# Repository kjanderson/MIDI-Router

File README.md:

# MIDI-Router
PIC24/FPGA code to route MIDI data on prototype hardware.

The objective of this project is to build a prototype that is able to route MIDI
signals from source to destination automatically.

The hardware provides 4 MIDI inputs, 4 MIDI thru's, and 4 MIDI outputs.
This software project implements the routing of the inputs to the outputs.

Notes
 - USB is copied from the MLA USB Framework
 - USB-app is copied from the application example in the MLA
 - USB-bsp is copied from the application example in the MLA

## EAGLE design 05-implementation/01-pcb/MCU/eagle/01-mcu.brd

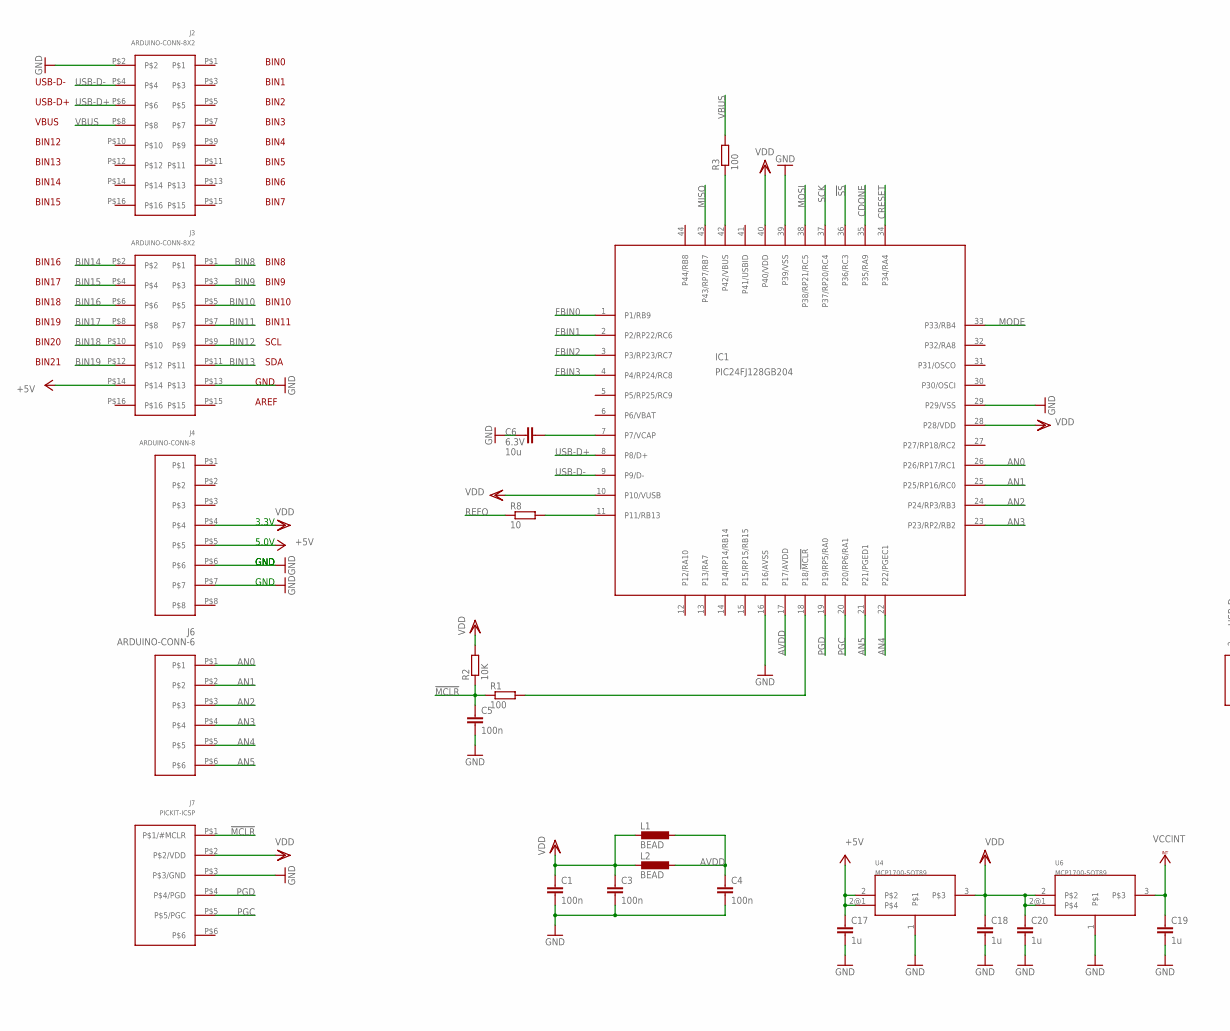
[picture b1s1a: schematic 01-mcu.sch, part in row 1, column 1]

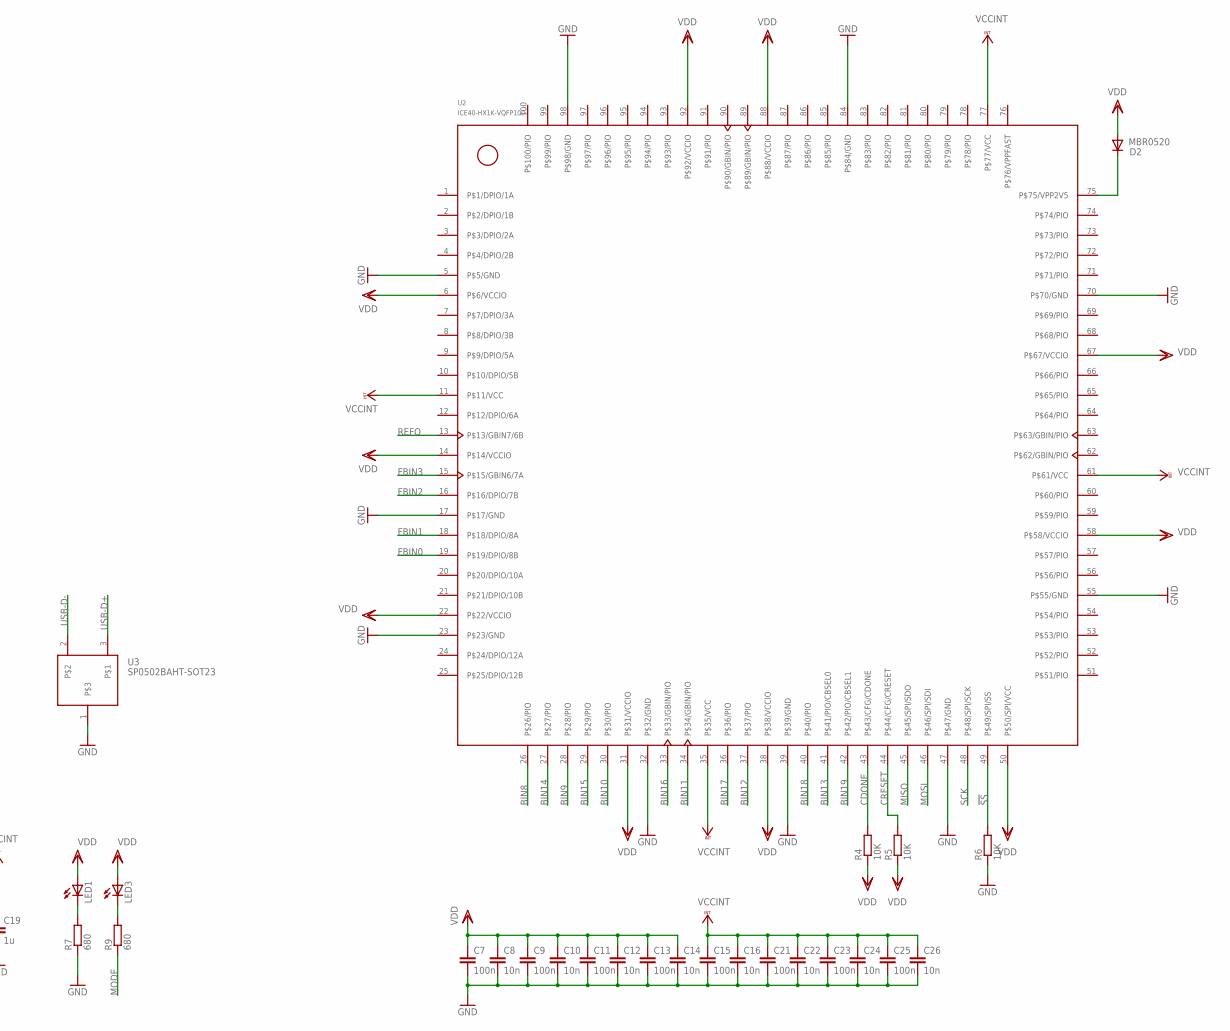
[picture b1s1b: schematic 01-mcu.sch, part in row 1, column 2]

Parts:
C1, C3, C4, C5, C7, C9, C11, C13, C15, C21, C23, C25: 100n; C0805
C6: 10u; C0805; RATING 6.3V
C8, C10, C12, C14, C16, C22, C24, C26: 10n; C0805
C17, C18, C19, C20: 1u; C0805
D2: MBR0520; MBR0520-SOD-123_MINI-SMA
IC1: PIC24FJ128GB204; TQFP44
J2, J3: ARDUINO-CONN-8X2
J4: ARDUINO-CONN-8
J6: ARDUINO-CONN-6
J7: PICKIT-ICSP
L1, L2: BEAD; L0805
LED1, LED3: LEDCHIP-LED0805; CHIP-LED0805
R1, R3: 100; R0805
R2, R4, R5, R6: 10K; R0805
R7, R9: 680; R0805
R8: 10; R0805
U2: ICE40-HX1K-VQFP100; TQFP100-14X14
U3: SP0502BAHT-SOT23; SOT23
U4, U6: MCP1700-SOT89

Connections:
!MCLR: C5.1, J7.P$1 (P$1/#MCLR), R1.1, R2.1
!SS: IC1.36 (P36/RC3), R6.2, U2.49 (P$49/SPI/SS)
+5V: C17.1, J3.P$14, J4.P$5, U4.2, U4.2@1
AN0: IC1.26 (P26/RP17/RC1), J6.P$1
AN1: IC1.25 (P25/RP16/RC0), J6.P$2
AN2: IC1.24 (P24/RP3/RB3), J6.P$3
AN3: IC1.23 (P23/RP2/RB2), J6.P$4
AN4: IC1.22 (P22/PGEC1), J6.P$5
AN5: IC1.21 (P21/PGED1), J6.P$6
AVDD: C4.1, IC1.17 (P17/AVDD), L1.2, L2.2
BIN8: J3.P$1, U2.26 (P$26/PIO)
BIN9: J3.P$3, U2.28 (P$28/PIO)
BIN10: J3.P$5, U2.30 (P$30/PIO)
BIN11: J3.P$7, U2.34 (P$34/GBIN/PIO)
BIN12: J3.P$9, U2.37 (P$37/PIO)
BIN13: J3.P$11, U2.41 (P$41/PIO/CBSEL0)
BIN14: J3.P$2, U2.27 (P$27/PIO)
BIN15: J3.P$4, U2.29 (P$29/PIO)
BIN16: J3.P$6, U2.33 (P$33/GBIN/PIO)
BIN17: J3.P$8, U2.36 (P$36/PIO)
BIN18: J3.P$10, U2.40 (P$40/PIO)
BIN19: J3.P$12, U2.42 (P$42/PIO/CBSEL1)
CDONE: IC1.35 (P35/RA9), R4.2, U2.43 (P$43/CFG/CDONE)
CRESET: IC1.34 (P34/RA4), R5.2, U2.44 (P$44/CFG/CRESET)
FBIN0: IC1.1 (P1/RB9), U2.19 (P$19/DPIO/8B)
FBIN1: IC1.2 (P2/RP22/RC6), U2.18 (P$18/DPIO/8A)
FBIN2: IC1.3 (P3/RP23/RC7), U2.16 (P$16/DPIO/7B)
FBIN3: IC1.4 (P4/RP24/RC8), U2.15 (P$15/GBIN6/7A)
GND: C1.2, C3.2, C4.2, C5.2, C6.1, C7.2, C8.2, C9.2, C10.2, C11.2, C12.2, C13.2, C14.2, C15.2, C16.2, C17.2, C18.2, C19.2, C20.2, C21.2, C22.2, C23.2, C24.2, C25.2, C26.2, IC1.16 (P16/AVSS), IC1.29 (P29/VSS), IC1.39 (P39/VSS), J2.P$2, J3.P$13, J4.P$6, J4.P$7, J7.P$3 (P$3/GND), R6.1, R7.1, U2.5 (P$5/GND), U2.17 (P$17/GND), U2.23 (P$23/GND), U2.32 (P$32/GND), U2.39 (P$39/GND), U2.47 (P$47/GND), U2.55 (P$55/GND), U2.70 (P$70/GND), U2.84 (P$84/GND), U2.98 (P$98/GND), U3.1, U4.1, U6.1
MISO: IC1.43 (P43/RP7/RB7), U2.45 (P$45/SPI/SDO)
MODE: IC1.33 (P33/RB4), R9.1
MOSI: IC1.38 (P38/RP21/RC5), U2.46 (P$46/SPI/SDI)
unnamed: IC1.42 (P42/VBUS), R3.1
unnamed: D2.C, U2.75 (P$75/VPP2V5)
unnamed: IC1.18 (P18/!MCLR), R1.2
unnamed: IC1.11 (P11/RB13), R8.2
unnamed: C6.2, IC1.7 (P7/VCAP)
unnamed: LED1.C, R7.2
unnamed: LED3.C, R9.2
PGC: IC1.20 (P20/RP6/RA1), J7.P$5 (P$5/PGC)
PGD: IC1.19 (P19/RP5/RA0), J7.P$4 (P$4/PGD)
REFO: R8.1, U2.13 (P$13/GBIN7/6B)
SCK: IC1.37 (P37/RP20/RC4), U2.48 (P$48/SPI/SCK)
USB-D+: IC1.8 (P8/D+), J2.P$6, U3.3
USB-D-: IC1.9 (P9/D-), J2.P$4, U3.2
VBUS: J2.P$8, R3.2
VCCINT: C15.1, C16.1, C19.1, C21.1, C22.1, C23.1, C24.1, C25.1, C26.1, U2.11 (P$11/VCC), U2.35 (P$35/VCC), U2.61 (P$61/VCC), U2.77 (P$77/VCC), U6.3
VDD: C1.1, C3.1, C7.1, C8.1, C9.1, C10.1, C11.1, C12.1, C13.1, C14.1, C18.1, C20.1, D2.A, IC1.10 (P10/VUSB), IC1.28 (P28/VDD), IC1.40 (P40/VDD), J4.P$4, J7.P$2 (P$2/VDD), L1.1, L2.1, LED1.A, LED3.A, R2.2, R4.1, R5.1, U2.6 (P$6/VCCIO), U2.14 (P$14/VCCIO), U2.22 (P$22/VCCIO), U2.31 (P$31/VCCIO), U2.38 (P$38/VCCIO), U2.50 (P$50/SPI/VCC), U2.58 (P$58/VCCIO), U2.67 (P$67/VCCIO), U2.88 (P$88/VCCIO), U2.92 (P$92/VCCIO), U4.3, U6.2, U6.2@1

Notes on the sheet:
3.3V
5.0V
GND
AREF
BIN0
BIN1
BIN2
BIN3
BIN4
BIN5
BIN6
BIN7
USB-D-
USB-D+
VBUS
BIN12
BIN13
BIN14
BIN15
BIN8
BIN9
BIN10
BIN11
SCL
SDA
BIN16
BIN17
BIN18
BIN19
BIN20
BIN21

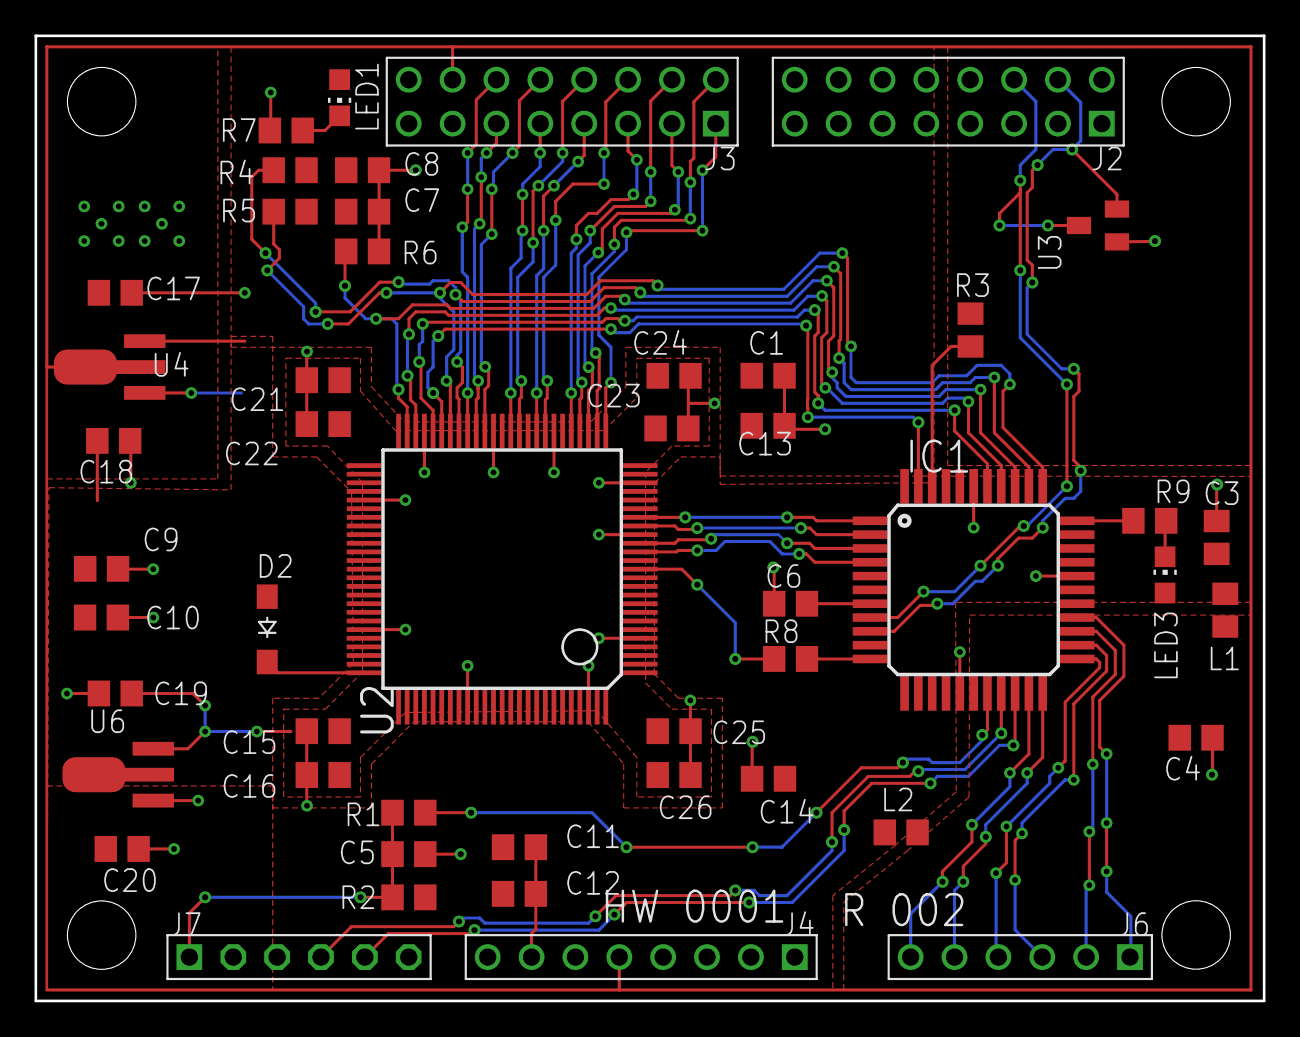
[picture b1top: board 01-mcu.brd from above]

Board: 2 copper layers, 71.1 x 55.9 mm, 49 parts (0 on the bottom side), 48 nets.

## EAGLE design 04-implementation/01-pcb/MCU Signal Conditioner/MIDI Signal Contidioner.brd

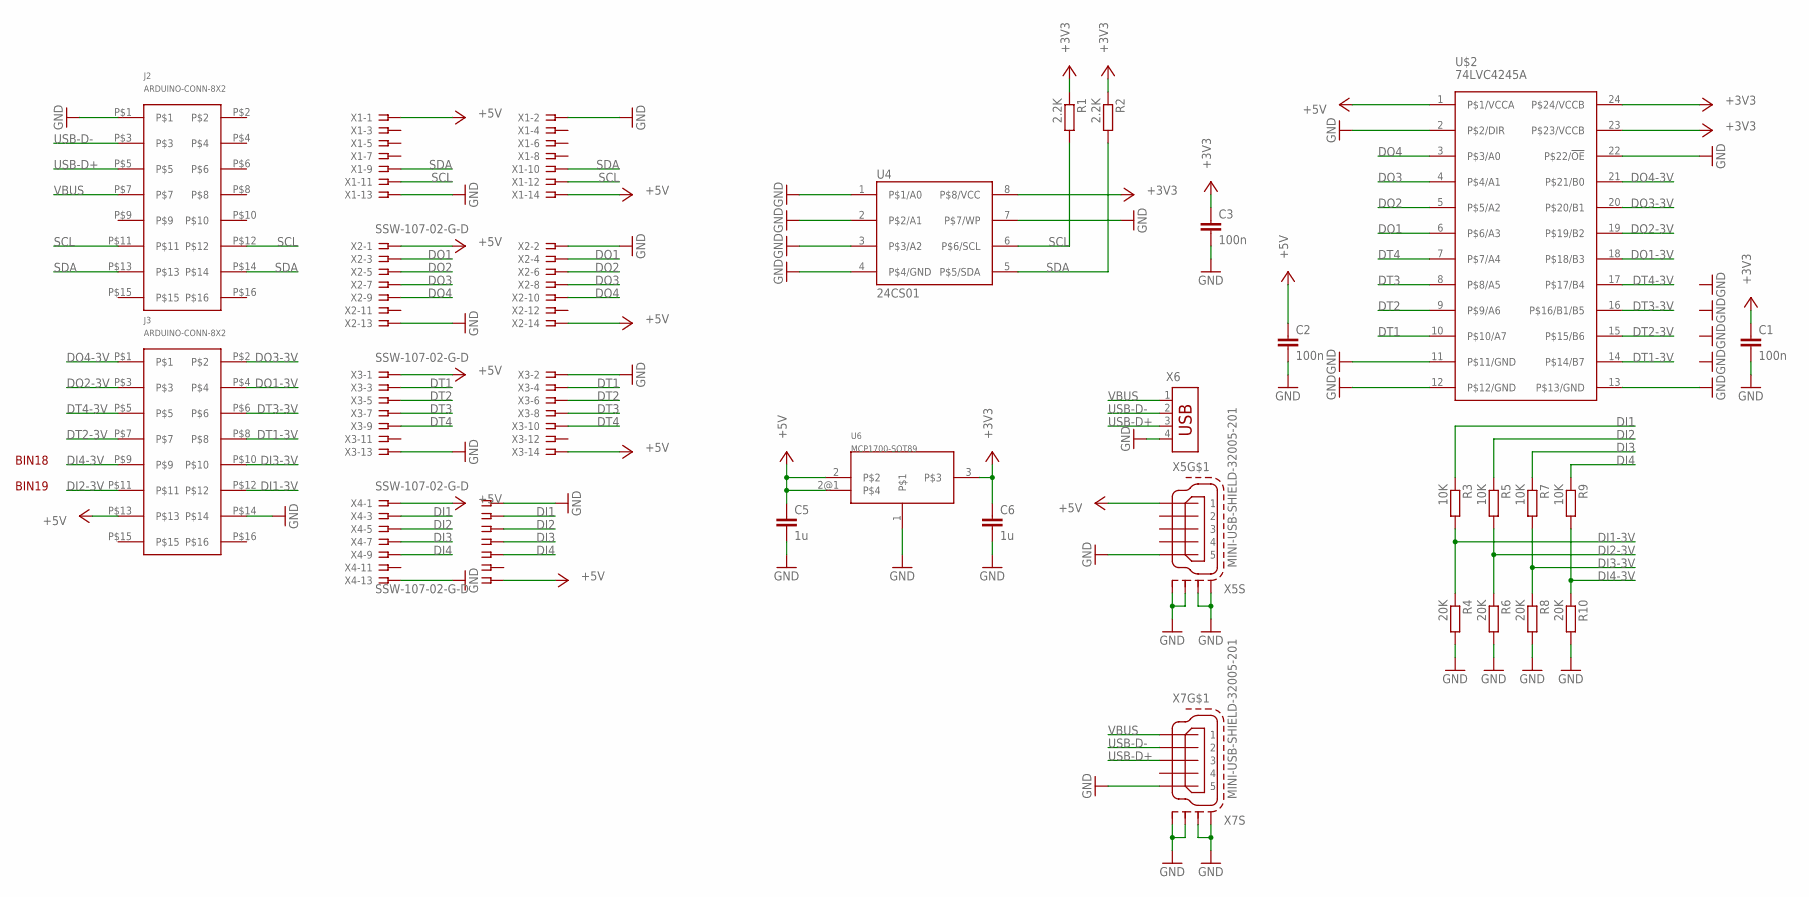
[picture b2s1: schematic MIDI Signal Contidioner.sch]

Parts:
C1, C2, C3: 100n; C0805
C5, C6: 1u; C0805
J2, J3: ARDUINO-CONN-8X2
R1, R2: 2.2K; R0805W
R3, R5, R7, R9: 10K; R0805W
R4, R6, R8, R10: 20K; R0805W
U4: 24CS01; 24CS01-SO8
U6: MCP1700-SOT89
U$2: 74LVC4245A; 74LVC4245A-SO24
X1, X2, X3, X4: SSW-107-02-G-D
X5, X7: MINI-USB-SHIELD-32005-201; MINI-USB-32005-201
X6: USB-787616; USB

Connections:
+3V3: C1.1, C3.1, C6.1, R1.1, R2.1, U4.8 (P$8/VCC), U6.3, U$2.23 (P$23/VCCB), U$2.24 (P$24/VCCB)
+5V: C2.1, C5.1, J3.P$13, U6.2, U6.2@1, U$2.1 (P$1/VCCA), X1.1, X1.14, X2.1, X2.14, X3.1, X3.14, X4.1, X4.14, X5.1
DI1: R3.1, X4.3, X4.4
DI1-3V: J3.P$12, R3.2, R4.1
DI2: R5.1, X4.5, X4.6
DI2-3V: J3.P$11, R5.2, R6.1
DI3: R7.1, X4.7, X4.8
DI3-3V: J3.P$10, R7.2, R8.1
DI4: R9.1, X4.9, X4.10
DI4-3V: J3.P$9, R9.2, R10.1
DO1: U$2.6 (P$6/A3), X2.3, X2.4
DO1-3V: J3.P$4, U$2.18 (P$18/B3)
DO2: U$2.5 (P$5/A2), X2.5, X2.6
DO2-3V: J3.P$3, U$2.19 (P$19/B2)
DO3: U$2.4 (P$4/A1), X2.7, X2.8
DO3-3V: J3.P$2, U$2.20 (P$20/B1)
DO4: U$2.3 (P$3/A0), X2.9, X2.10
DO4-3V: J3.P$1, U$2.21 (P$21/B0)
DT1: U$2.10 (P$10/A7), X3.3, X3.4
DT1-3V: J3.P$8, U$2.14 (P$14/B7)
DT2: U$2.9 (P$9/A6), X3.5, X3.6
DT2-3V: J3.P$7, U$2.15 (P$15/B6)
DT3: U$2.8 (P$8/A5), X3.7, X3.8
DT3-3V: J3.P$6, U$2.16 (P$16/B1/B5)
DT4: U$2.7 (P$7/A4), X3.9, X3.10
DT4-3V: J3.P$5, U$2.17 (P$17/B4)
GND: C1.2, C2.2, C3.2, C5.2, C6.2, J2.P$1, J3.P$14, R4.2, R6.2, R8.2, R10.2, U4.1 (P$1/A0), U4.2 (P$2/A1), U4.3 (P$3/A2), U4.4 (P$4/GND), U4.7 (P$7/WP), U6.1, U$2.2 (P$2/DIR), U$2.11 (P$11/GND), U$2.12 (P$12/GND), U$2.13 (P$13/GND), U$2.22 (P$22/!OE), X1.2, X1.13, X2.2, X2.13, X3.2, X3.13, X4.2, X4.13, X5.5, X5.M1 (S1), X5.M2 (S2), X5.M3 (S3), X5.M4 (S4), X6.4, X7.5, X7.M1 (S1), X7.M2 (S2), X7.M3 (S3), X7.M4 (S4)
SCL: J2.P$11, J2.P$12, R1.2, U4.6 (P$6/SCL), X1.11, X1.12
SDA: J2.P$13, J2.P$14, R2.2, U4.5 (P$5/SDA), X1.9, X1.10
USB-D+: J2.P$5, X6.3, X7.3
USB-D-: J2.P$3, X6.2, X7.2
VBUS: J2.P$7, X6.1, X7.1

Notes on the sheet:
BIN18
BIN19

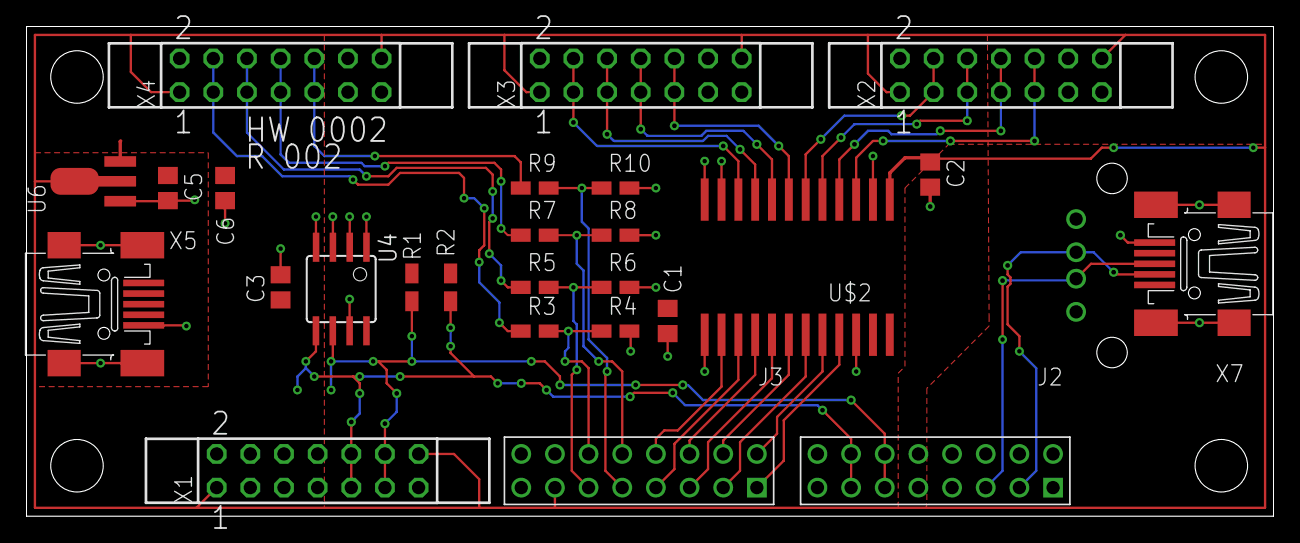
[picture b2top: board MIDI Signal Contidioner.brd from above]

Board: 2 copper layers, 94.1 x 37.0 mm, 27 parts (1 on the bottom side), 32 nets.

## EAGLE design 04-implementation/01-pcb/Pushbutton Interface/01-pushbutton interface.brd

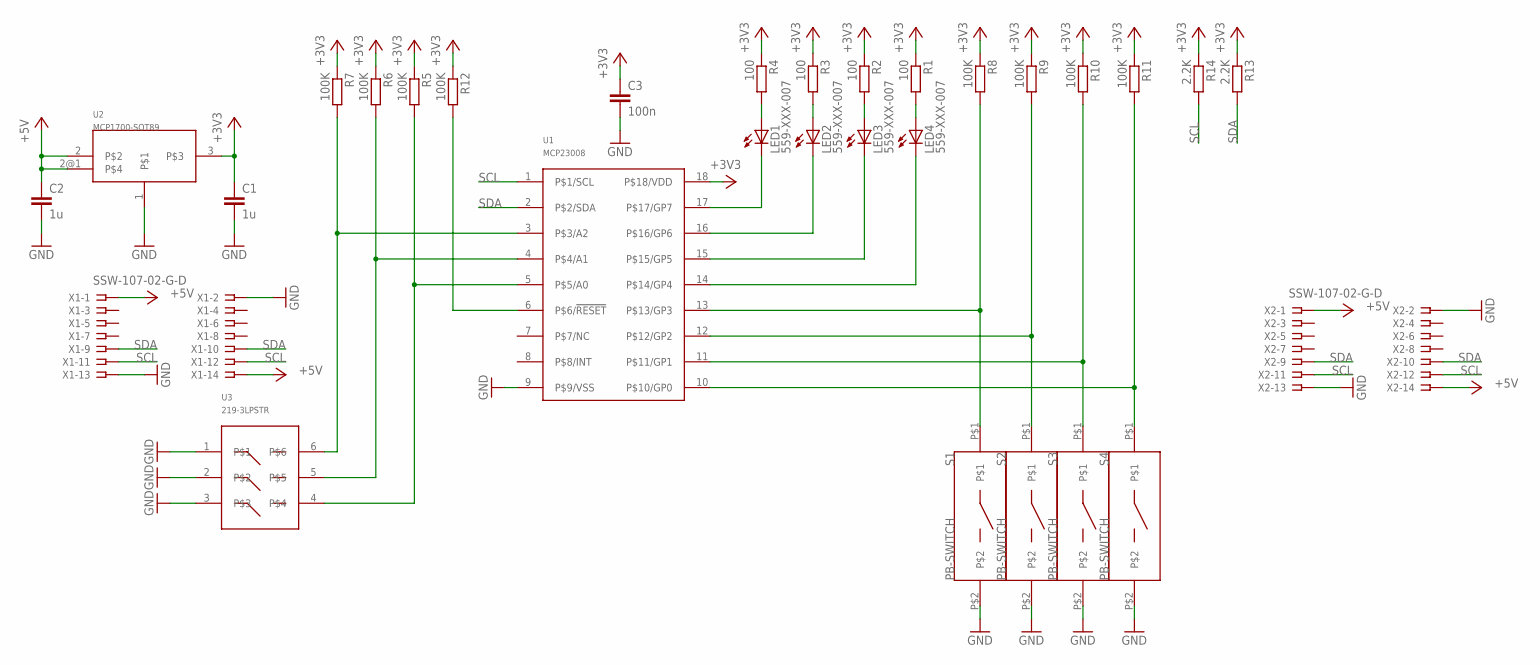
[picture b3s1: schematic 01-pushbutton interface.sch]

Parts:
C1, C2: 1u; C0805
C3: 100n; C0805
LED1, LED2, LED3, LED4: 559-XXX-007; LED
R1, R2, R3, R4: 100; R0805
R5, R6, R7, R8, R9, R10, R11, R12: 100K; R0805
R13, R14: 2.2K; R0805
S1, S2, S3, S4: PB-SWITCH; SWITCH
U1: MCP23008; MCP23008-SO18
U2: MCP1700-SOT89
U3: 219-3LPSTR
X1, X2: SSW-107-02-G-D

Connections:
+3V3: C1.1, C3.1, R1.1, R2.1, R3.1, R4.1, R5.1, R6.1, R7.1, R8.1, R9.1, R10.1, R11.1, R12.1, R13.1, R14.1, U1.18 (P$18/VDD), U2.3
+5V: C2.1, U2.2, U2.2@1, X1.1, X1.14, X2.1, X2.14
GND: C1.2, C2.2, C3.2, S1.P$2, S2.P$2, S3.P$2, S4.P$2, U1.9 (P$9/VSS), U2.1, U3.1, U3.2, U3.3, X1.2, X1.13, X2.2, X2.13
unnamed: R8.2, S1.P$1, U1.13 (P$13/GP3)
unnamed: R9.2, S2.P$1, U1.12 (P$12/GP2)
unnamed: LED4.P$1 (A), R1.2
unnamed: LED3.P$1 (A), R2.2
unnamed: LED2.P$1 (A), R3.2
unnamed: LED1.P$1 (A), R4.2
unnamed: LED1.P$2 (C), U1.17 (P$17/GP7)
unnamed: LED2.P$2 (C), U1.16 (P$16/GP6)
unnamed: LED3.P$2 (C), U1.15 (P$15/GP5)
unnamed: LED4.P$2 (C), U1.14 (P$14/GP4)
unnamed: R7.2, U1.3 (P$3/A2), U3.6
unnamed: R6.2, U1.4 (P$4/A1), U3.5
unnamed: R5.2, U1.5 (P$5/A0), U3.4
unnamed: R10.2, S3.P$1, U1.11 (P$11/GP1)
unnamed: R11.2, S4.P$1, U1.10 (P$10/GP0)
unnamed: R12.2, U1.6 (P$6/!RESET)
SCL: R14.2, U1.1 (P$1/SCL), X1.11, X1.12, X2.11, X2.12
SDA: R13.2, U1.2 (P$2/SDA), X1.9, X1.10, X2.9, X2.10

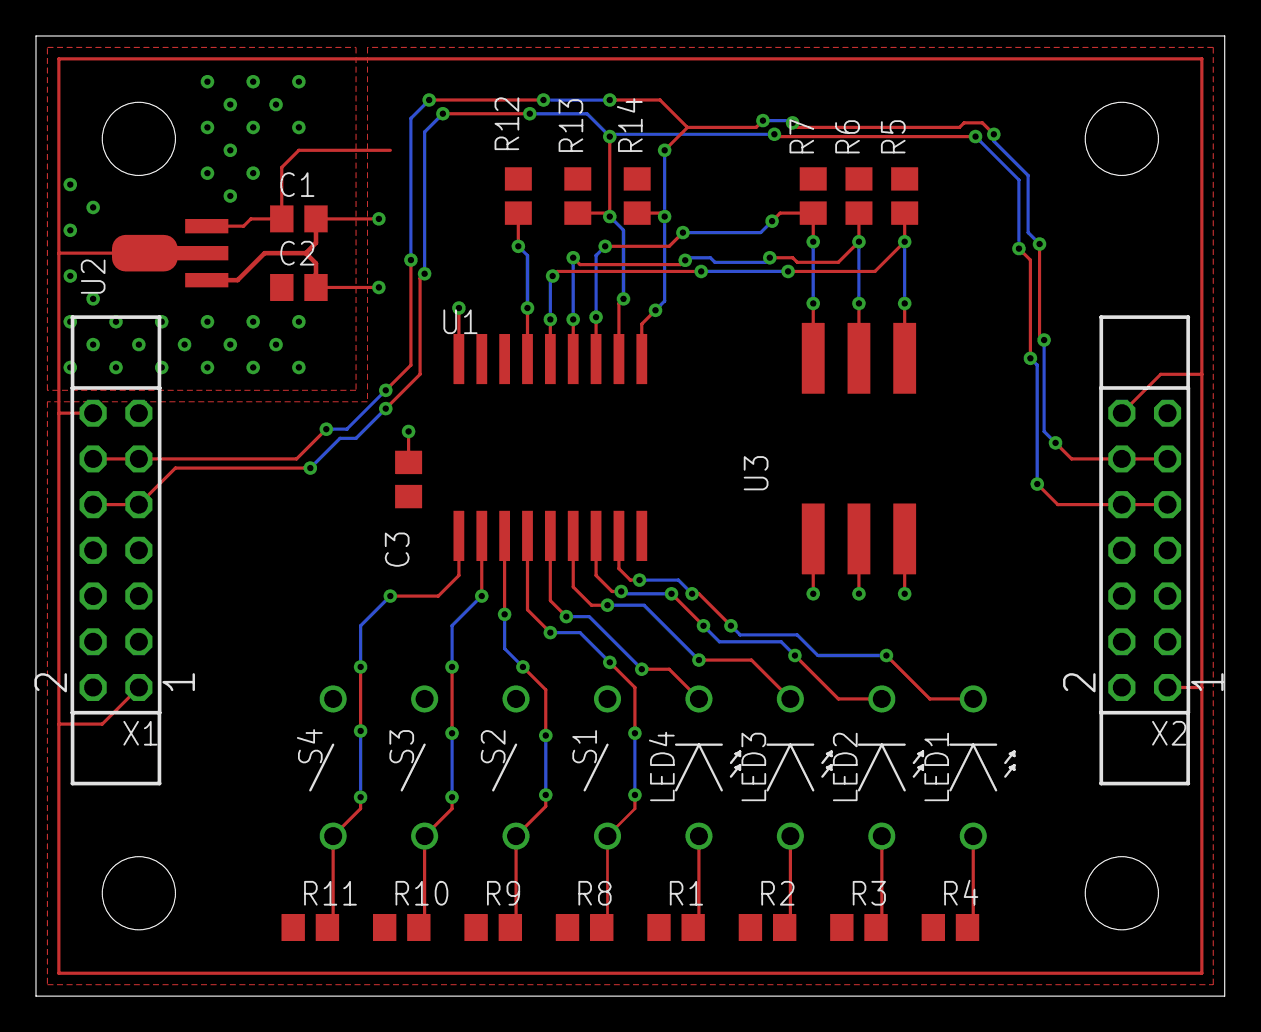
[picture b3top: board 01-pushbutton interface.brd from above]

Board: 2 copper layers, 66.0 x 53.3 mm, 30 parts (0 on the bottom side), 21 nets.

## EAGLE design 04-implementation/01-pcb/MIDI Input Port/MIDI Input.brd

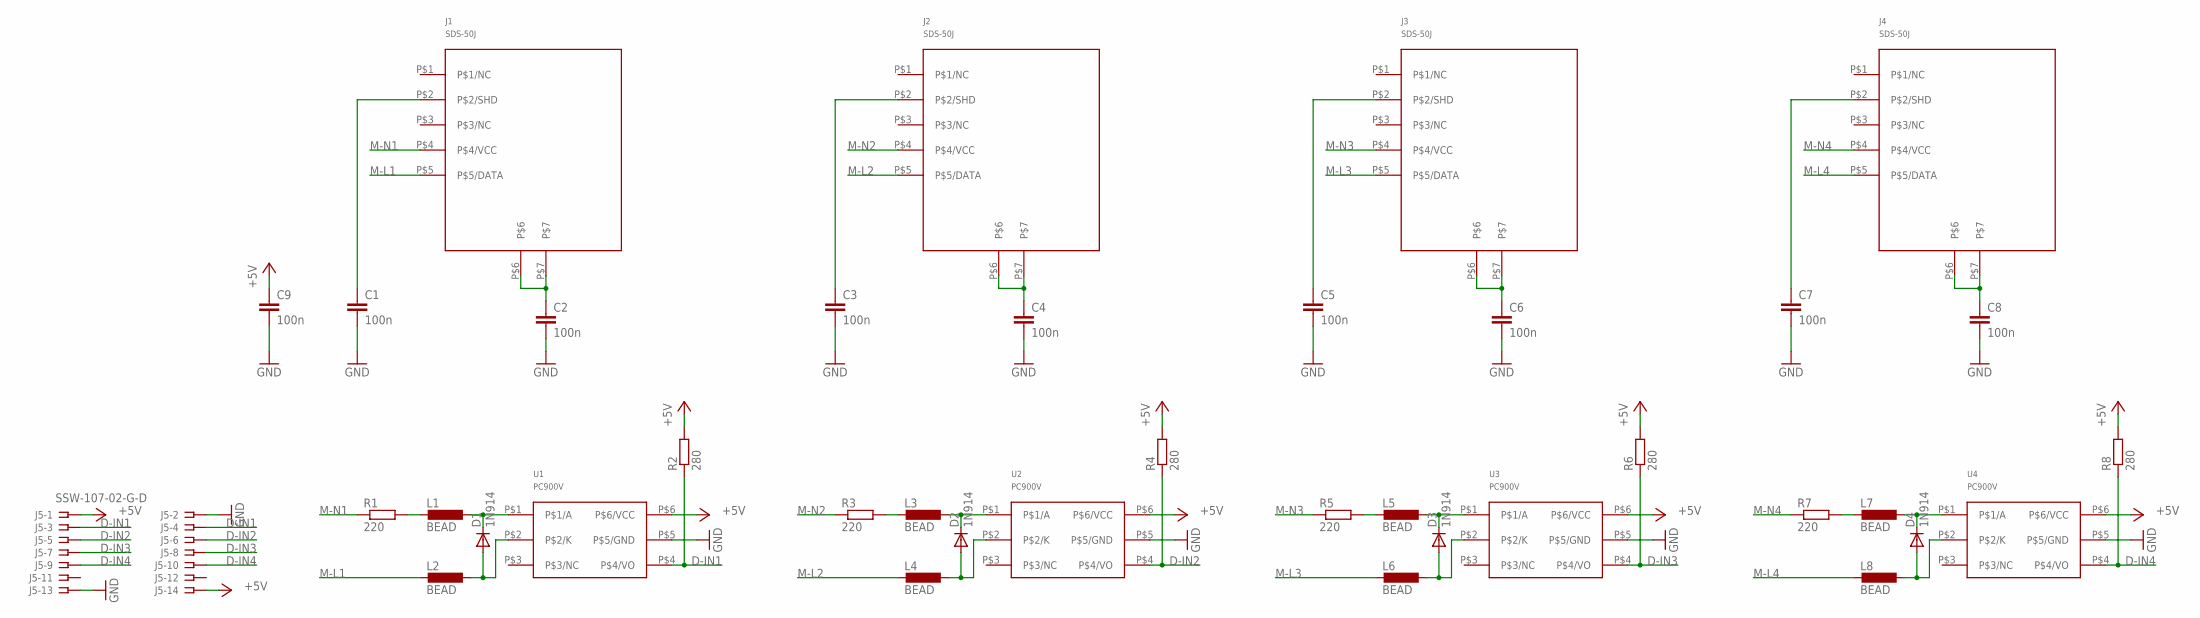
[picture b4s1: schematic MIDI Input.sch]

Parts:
C1, C2, C3, C4, C5, C6, C7, C8, C9: 100n; C0805
D1, D2, D3, D4: 1N914; SOD323-W
J1, J2, J3, J4: SDS-50J
J5: SSW-107-02-G-D
L1, L2, L3, L4, L5, L6, L7, L8: BEAD; L0805
R1, R3, R5, R7: 220; R0805
R2, R4, R6, R8: 280; R0805
U1, U2, U3, U4: PC900V; DIL06

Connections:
+5V: C9.1, J5.1, J5.14, R2.2, R4.2, R6.2, R8.2, U1.P$6 (P$6/VCC), U2.P$6 (P$6/VCC), U3.P$6 (P$6/VCC), U4.P$6 (P$6/VCC)
D-IN1: J5.3, J5.4, R2.1, U1.P$4 (P$4/VO)
D-IN2: J5.5, J5.6, R4.1, U2.P$4 (P$4/VO)
D-IN3: J5.7, J5.8, R6.1, U3.P$4 (P$4/VO)
D-IN4: J5.9, J5.10, R8.1, U4.P$4 (P$4/VO)
GND: C1.2, C2.2, C3.2, C4.2, C5.2, C6.2, C7.2, C8.2, C9.2, J5.2, J5.13, U1.P$5 (P$5/GND), U2.P$5 (P$5/GND), U3.P$5 (P$5/GND), U4.P$5 (P$5/GND)
M-L1: J1.P$5 (P$5/DATA), L2.1
M-L2: J2.P$5 (P$5/DATA), L4.1
M-L3: J3.P$5 (P$5/DATA), L6.1
M-L4: J4.P$5 (P$5/DATA), L8.1
M-N1: J1.P$4 (P$4/VCC), R1.1
M-N2: J2.P$4 (P$4/VCC), R3.1
M-N3: J3.P$4 (P$4/VCC), R5.1
M-N4: J4.P$4 (P$4/VCC), R7.1
unnamed: L1.1, R1.2
unnamed: D1.C, L1.2, U1.P$1 (P$1/A)
unnamed: D1.A, L2.2, U1.P$2 (P$2/K)
unnamed: D2.C, L3.2, U2.P$1 (P$1/A)
unnamed: C2.1, J1.P$6, J1.P$7
unnamed: D2.A, L4.2, U2.P$2 (P$2/K)
unnamed: C4.1, J2.P$6, J2.P$7
unnamed: C1.1, J1.P$2 (P$2/SHD)
unnamed: C3.1, J2.P$2 (P$2/SHD)
unnamed: L3.1, R3.2
unnamed: D3.C, L5.2, U3.P$1 (P$1/A)
unnamed: D3.A, L6.2, U3.P$2 (P$2/K)
unnamed: C6.1, J3.P$6, J3.P$7
unnamed: C5.1, J3.P$2 (P$2/SHD)
unnamed: L5.1, R5.2
unnamed: D4.C, L7.2, U4.P$1 (P$1/A)
unnamed: D4.A, L8.2, U4.P$2 (P$2/K)
unnamed: C8.1, J4.P$6, J4.P$7
unnamed: C7.1, J4.P$2 (P$2/SHD)
unnamed: L7.1, R7.2

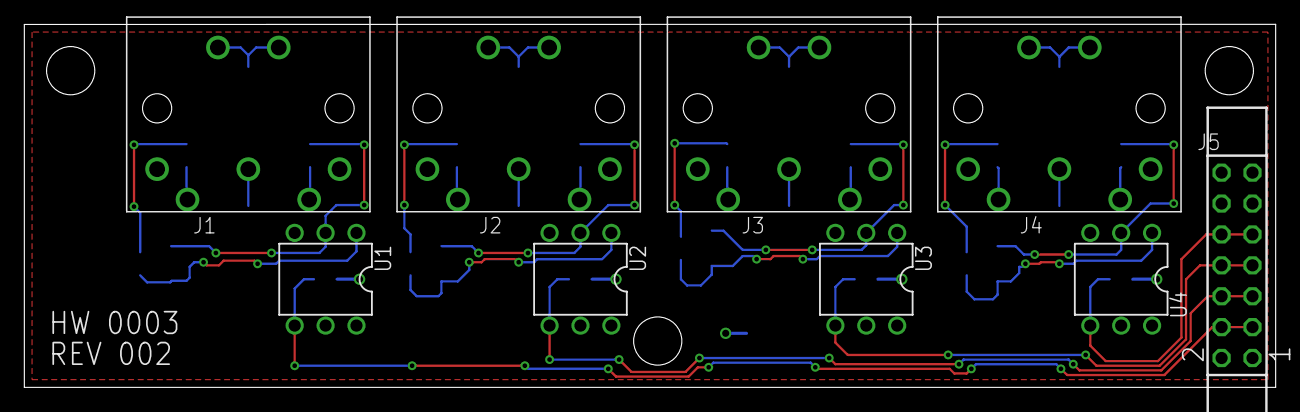
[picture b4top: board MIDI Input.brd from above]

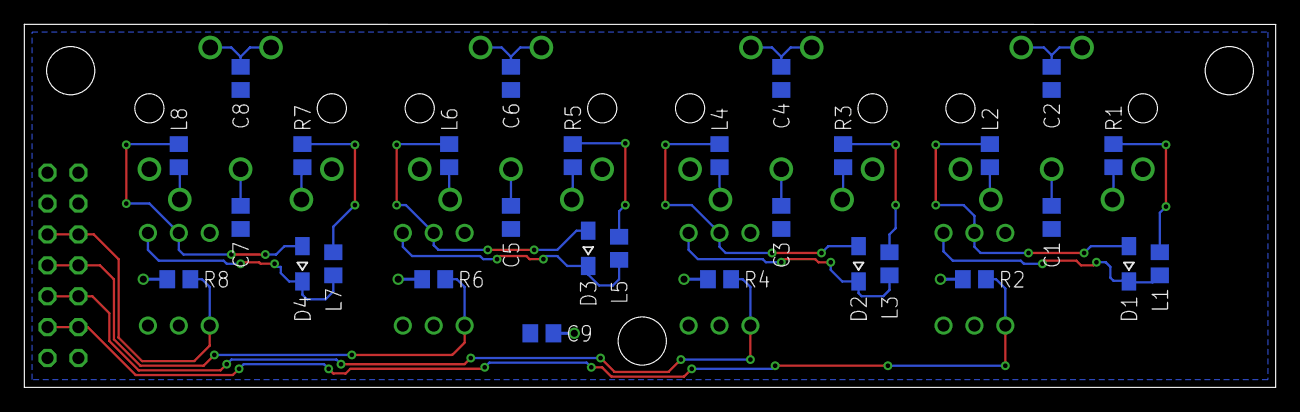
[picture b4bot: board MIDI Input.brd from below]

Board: 2 copper layers, 102.9 x 29.8 mm, 38 parts (29 on the bottom side), 34 nets.

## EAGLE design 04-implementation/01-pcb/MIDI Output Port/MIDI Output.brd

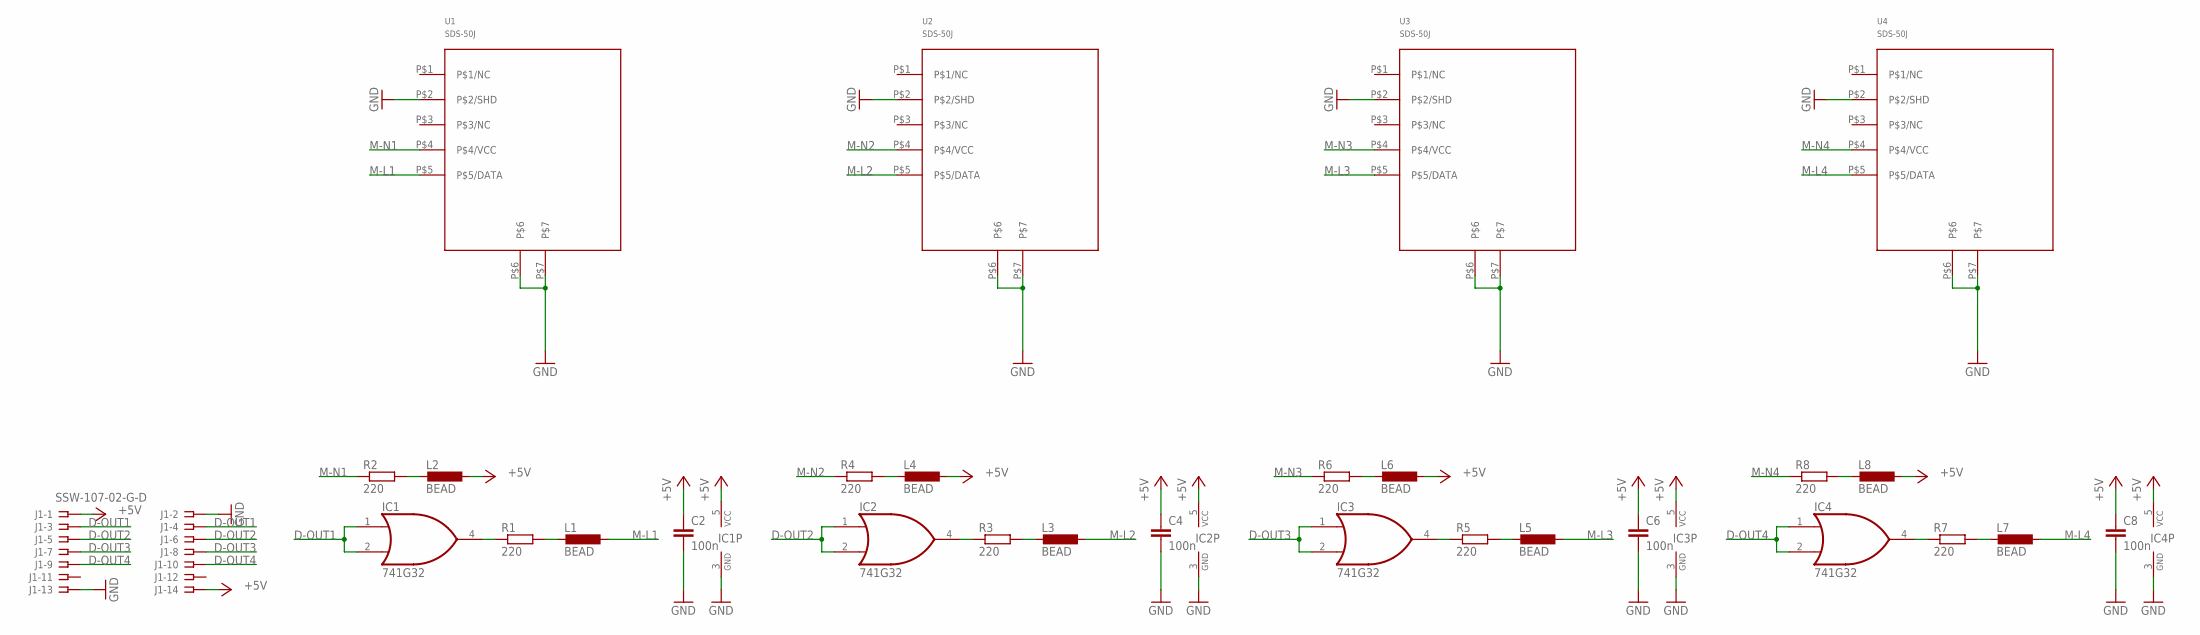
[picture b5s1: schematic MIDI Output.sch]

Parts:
C2, C4, C6, C8: 100n; C0805
IC1, IC2, IC3, IC4: 741G32; SOT25
J1: SSW-107-02-G-D
L1, L2, L3, L4, L5, L6, L7, L8: BEAD; L0805
R1, R2, R3, R4, R5, R6, R7, R8: 220; R0805
U1, U2, U3, U4: SDS-50J

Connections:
+5V: C2.1, C4.1, C6.1, C8.1, IC1.5 (VCC), IC2.5 (VCC), IC3.5 (VCC), IC4.5 (VCC), J1.1, J1.14, L2.2, L4.2, L6.2, L8.2
D-OUT1: IC1.1 (I0), IC1.2 (I1), J1.3, J1.4
D-OUT2: IC2.1 (I0), IC2.2 (I1), J1.5, J1.6
D-OUT3: IC3.1 (I0), IC3.2 (I1), J1.7, J1.8
D-OUT4: IC4.1 (I0), IC4.2 (I1), J1.9, J1.10
GND: C2.2, C4.2, C6.2, C8.2, IC1.3 (GND), IC2.3 (GND), IC3.3 (GND), IC4.3 (GND), J1.2, J1.13, U1.P$2 (P$2/SHD), U1.P$6, U1.P$7, U2.P$2 (P$2/SHD), U2.P$6, U2.P$7, U3.P$2 (P$2/SHD), U3.P$6, U3.P$7, U4.P$2 (P$2/SHD), U4.P$6, U4.P$7
M-L1: L1.2, U1.P$5 (P$5/DATA)
M-L2: L3.2, U2.P$5 (P$5/DATA)
M-L3: L5.2, U3.P$5 (P$5/DATA)
M-L4: L7.2, U4.P$5 (P$5/DATA)
M-N1: R2.1, U1.P$4 (P$4/VCC)
M-N2: R4.1, U2.P$4 (P$4/VCC)
M-N3: R6.1, U3.P$4 (P$4/VCC)
M-N4: R8.1, U4.P$4 (P$4/VCC)
unnamed: IC1.4 (O), R1.1
unnamed: L2.1, R2.2
unnamed: L1.1, R1.2
unnamed: L3.1, R3.2
unnamed: L4.1, R4.2
unnamed: IC2.4 (O), R3.1
unnamed: L5.1, R5.2
unnamed: L6.1, R6.2
unnamed: IC3.4 (O), R5.1
unnamed: L7.1, R7.2
unnamed: L8.1, R8.2
unnamed: IC4.4 (O), R7.1

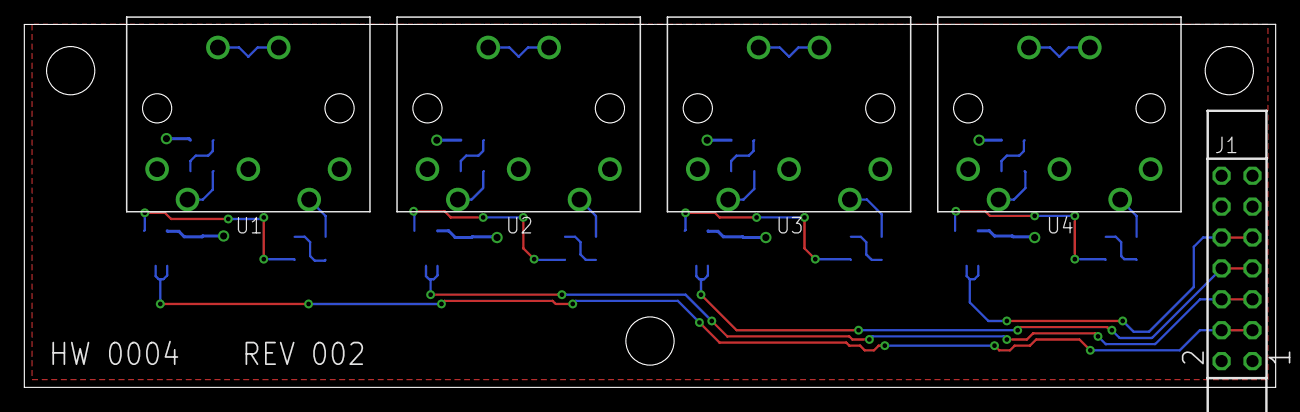
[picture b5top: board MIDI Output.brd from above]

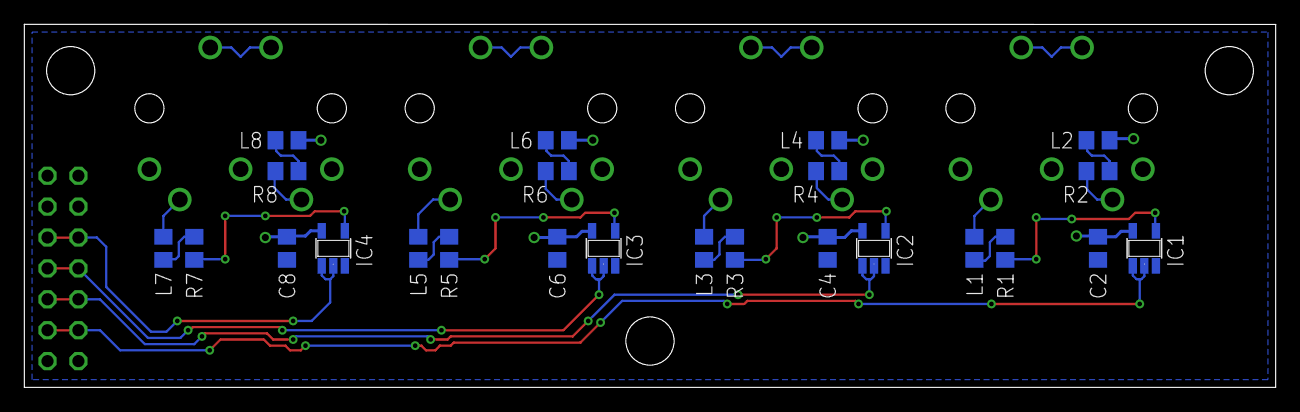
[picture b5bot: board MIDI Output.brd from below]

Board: 2 copper layers, 102.9 x 29.8 mm, 29 parts (24 on the bottom side), 26 nets.

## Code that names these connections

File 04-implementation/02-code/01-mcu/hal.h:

#ifndef HAL_H
#define HAL_H

#include <xc.h>
#include <stdint.h>

#define HAL_INSNS_PER_SECTOR 512
#define HAL_BYTES_PER_INSN 3
#define HAL_INSNS_PER_PAGE 64
#define HAL_BYTES_PER_SECTOR ((HAL_INSNS_PER_SECTOR) * (HAL_BYTES_PER_INSN))
#define HAL_BYTES_PER_PAGE ((HAL_INSNS_PER_PAGE) * (HAL_BYTES_PER_INSN))

/* utility functions */
#define HAL_DIM(x) (sizeof((x))/sizeof((x[0])))

/* interrupt interface */
#define Hal_IrqDisable() __builtin_disi(0x3FFF)
#define Hal_IrqEnable() __builtin_disi(0x0000)

/* watchdog interface */
#define Hal_WatchdogReset() ClrWdt()
#define Hal_WatchdogEnable() (RCONbits.SWDTEN = 1)
#define Hal_WatchdogDisable() (RCONbits.SWDTEN = 0)

/* GPIO interface */
/* CRESET is active low */
/* Pin 34 (RA4) is input only, and compiler support for TRIS A4 was removed */
/* Until the PCB is corrected, SW won't be able to drive the reset pin */
#define Hal_GpioSetReset()
#define Hal_GpioClrReset()
#define Hal_GpioEnableOutputReset()
#define Hal_GpioDisableOutputReset()
/* CDONE is active high */
#define Hal_GpioGetDone() (PORTA & _LATA_LATA9_MASK)
#define Hal_GpioDisableOutputDone() (TRISAbits.TRISA9 = 1)
/* SPI_SS is active low */
#define Hal_GpioSetCfgSpiSs() (LATCbits.LATC3 = 0)
#define Hal_GpioClrCfgSpiSs() (LATCbits.LATC3 = 1)
#define Hal_GpioEnableOutputSpiSs() (TRISCbits.TRISC3 = 0)
#define Hal_GpioDisableOutputSpiSs() (TRISCbits.TRISC3 = 1)
/* FBIN0 */
#define Hal_GpioGetFbin0() (PORTBbits.RB9)
#define Hal_GpioEnableOutputFbin0() (TRISBbits.TRISB9 = 0)
#define Hal_GpioDisableOutputFbin0() (TRISBbits.TRISB9 = 1)
#define Hal_GpioSetFbin0() (LATBbits.LATB9 = 1)
#define Hal_GpioClrFbin0() (LATBbits.LATB9 = 0)
/* FBIN1 */
#define Hal_GpioGetFbin1() (PORTCbits.RC6)
#define Hal_GpioEnableOutputFbin1() (TRISCbits.TRISC6 = 0)
#define Hal_GpioDisableOutputFbin1() (TRISCbits.TRISC6 = 1)
#define Hal_GpioSetFbin1() (LATCbits.LATC6 = 1)
#define Hal_GpioClrFbin1() (LATCbits.LATC6 = 0)
/* FBIN2 */
#define Hal_GpioGetFbin2() (PORTCbits.RC7)
#define Hal_GpioEnableOutputFbin2() (TRISCbits.TRISC7 = 0)
#define Hal_GpioDisableOutputFbin2() (TRISCbits.TRISC7 = 1)
#define Hal_GpioSetFbin2() (LATCbits.LATC7 = 1)
#define Hal_GpioClrFbin2() (LATCbits.LATC7 = 0)
/* FBIN3 */
#define Hal_GpioGetFbin3() (PORTCbits.RC8)
#define Hal_GpioEnableOutputFbin3() (TRISCbits.TRISC8 = 0)
#define Hal_GpioDisableOutputFbin3() (TRISCbits.TRISC8 = 1)
#define Hal_GpioSetFbin3() (LATCbits.LATC8 = 1)
#define Hal_GpioClrFbin3() (LATCbits.LATC8 = 0)
/* LED is active low */
#define Hal_GpioSetMode() (LATAbits.LATA8 = 0)
#define Hal_GpioClrMode() (LATAbits.LATA8 = 1)
#define Hal_LedModeOn()   (LATAbits.LATA8 = 0)
#define Hal_LedModeOff()  (LATAbits.LATA8 = 1)
#define Hal_GpioEnableOutputMode() (TRISAbits.TRISA8 = 0)
#define Hal_GpioDisableOutputMode() (TRISAbits.TRISA8 = 1)

/* Timer interface */
#define Hal_Timer1Disable() (T1CON &= ~(_T1CON_TON_MASK))
#define Hal_Timer1Enable() (T1CON |= _T1CON_TON_MASK)
#define Hal_Timer1IsExpired() (IFS0 & _IFS0_T1IF_MASK)
#define Hal_Timer1Clear() (IFS0 &= ~(_IFS0_T1IF_MASK))
#define Hal_Timer1Restart() (TMR1 = 0)

/* SPI interface */
#define Hal_Spi1TxBusy() ((SPI1STATL & _SPI1STATL_SPIRBF_MASK) == 0)
//#define Hal_SpiSetTxData(x) (SPI1BUFL = (x); SPI1BUFH = 0)
void Hal_SpiSetTxData(uint8_t uData);
#define Hal_SpiGetRxData() (SPI1BUFL)
#define Hal_Spi1ClrInt() (IFS0 &= ~(_IFS0_U1RXIF_MASK))

/* USB interface */
#define Hal_UsbDisableVbusPort() (TRISB |= _TRISB_TRISB7_MASK)

uint8_t Hal_InitFpga(void);
void Hal_InitPeripherals(void);
void Hal_InitInterrupts(void);
void Hal_SpiInitForFpga(void);
void Hal_Timer1Config(uint16_t uTicks, uint8_t uFlags);
void Hal_IdleTasks(void);
void Hal_EraseFlashSector(uint32_t uBaseAddress);
void Hal_WriteFlashPage(uint32_t uBaseAddress, uint8_t *vuData);

#endif /* HAL_H */

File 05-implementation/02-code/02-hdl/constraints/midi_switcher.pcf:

# ##############################################################################

# iCEcube PCF

# Version:            2017.08.27940

# File Generated:     Feb 17 2018 06:34:16

# Family & Device:    iCE40HX1K

# Package:            VQ100

# ##############################################################################

###IOSet List 43
set_io clk 13
set_io gpio_fbin0 19
set_io gpio_fbin1 18
set_io gpio_fbin2 16
set_io gpio_fbin3 15
#set_io gpio_bin[0] 21
#set_io gpio_bin[1] 20
#set_io gpio_bin[2] 19
#set_io gpio_bin[3] 18
#set_io gpio_bin[0] 20
#set_io gpio_bin[1] 21
#set_io gpio_bin[2] 24
#set_io gpio_bin[3] 25
set_io midi_out[0] 26
set_io midi_out[2] 28
set_io midi_in[2] 30
set_io midi_in[0] 34
#set_io gpio_bin[8] 37
#set_io gpio_bin[9] 41
set_io midi_out[1] 27
set_io midi_out[3] 29
set_io midi_in[3] 33
set_io midi_in[1] 36
#set_io gpio_bin[14] 40
#set_io gpio_bin[15] 42
set_io spi_clk 48
set_io spi_miso 45
set_io spi_mosi 46
set_io spi_ss 49
